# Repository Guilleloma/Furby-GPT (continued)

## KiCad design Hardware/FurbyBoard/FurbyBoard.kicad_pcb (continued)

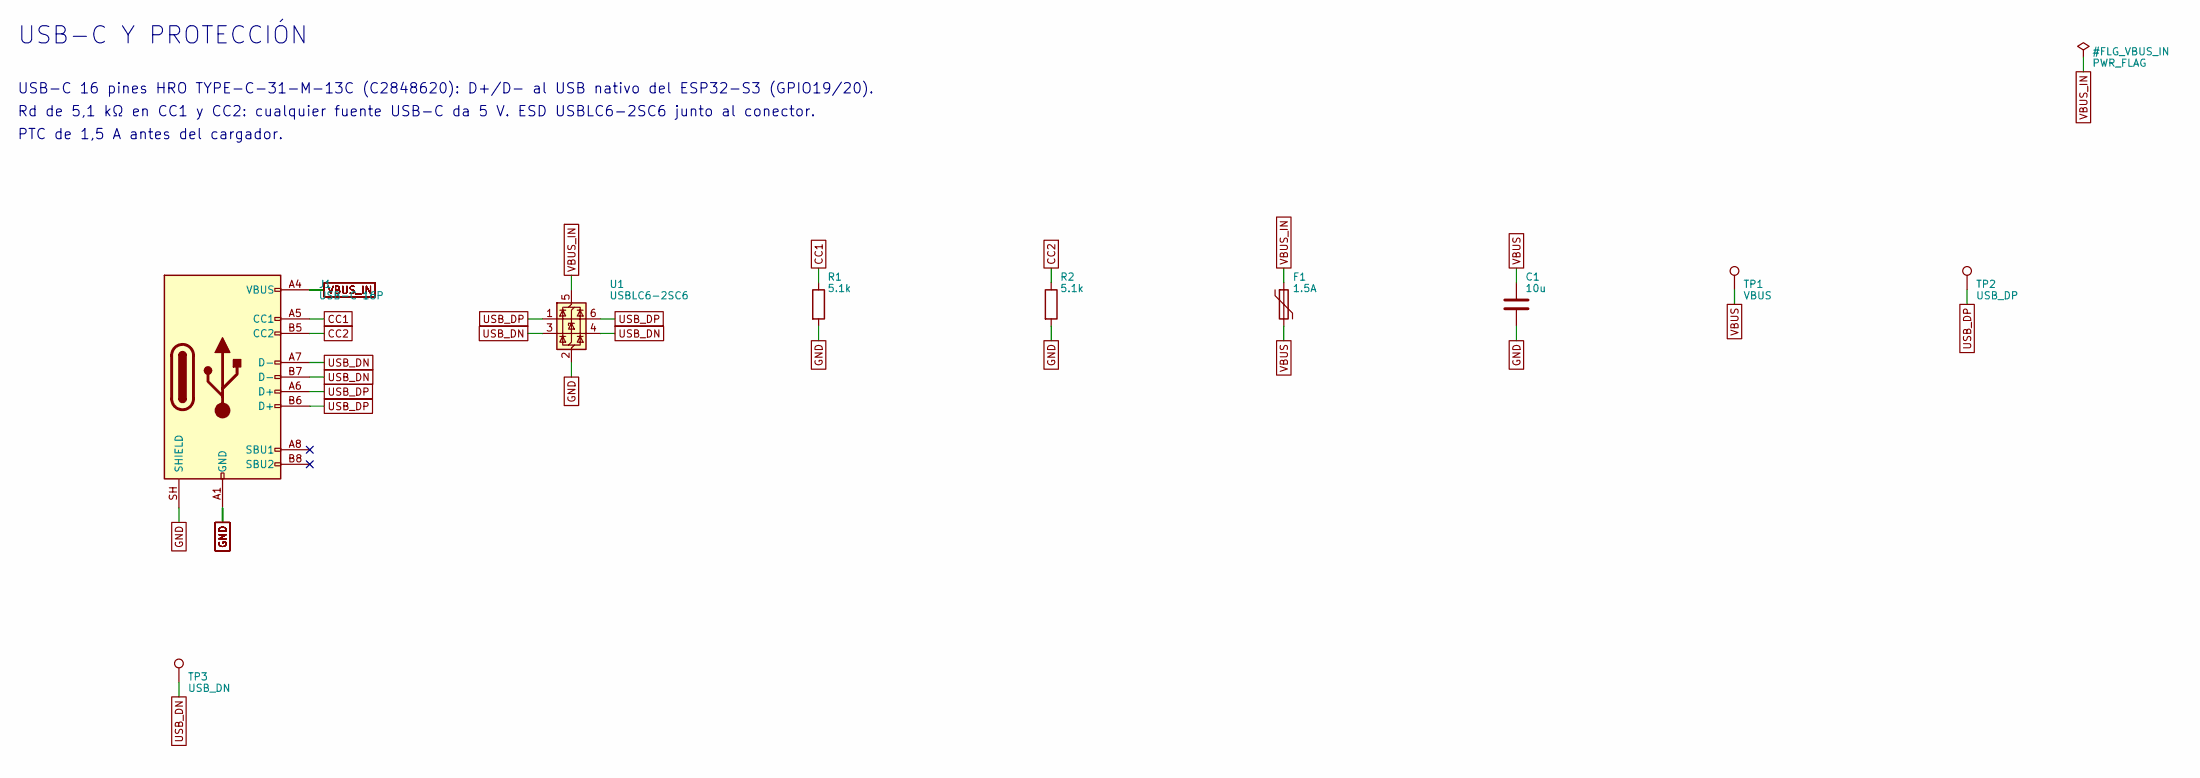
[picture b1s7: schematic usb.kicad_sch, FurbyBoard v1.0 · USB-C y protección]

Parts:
C1: 10u; C_0603_1608Metric; MPN 10 µF 10 V X5R; LCSC C19702
F1: 1.5A; Fuse_1206_3216Metric; MPN BSMD1206-150-16V; LCSC C883133
J1: USB-C 16P; USB_C_HRO_TYPE-C-31-M-13C; MPN HRO TYPE-C-31-M-13C; LCSC C2848620
R1, R2: 5.1k; R_0603_1608Metric; MPN UNI-ROYAL 0603 1%; LCSC C23186
TP1: VBUS; TestPoint_Pad_D1.5mm
TP2: USB_DP; TestPoint_Pad_D1.5mm
TP3: USB_DN; TestPoint_Pad_D1.5mm
U1: USBLC6-2SC6; SOT-23-6; MPN STMicro USBLC6-2SC6; LCSC C2687116

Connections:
CC1: J1.A5 (CC1), R1.1
CC2: J1.B5 (CC2), R2.1
GND: C1.2, J1.A1 (GND), J1.A12 (GND), J1.B1 (GND), J1.B12 (GND), J1.SH (SHIELD), R1.2, R2.2, U1.2 (GND); also elsewhere on the board
USB_DN: J1.A7 (D-), J1.B7 (D-), TP3.1, U1.3 (I/O2), U1.4 (I/O2); also elsewhere on the board
USB_DP: J1.A6 (D+), J1.B6 (D+), TP2.1, U1.1 (I/O1), U1.6 (I/O1); also elsewhere on the board
VBUS: C1.1, F1.2, TP1.1; also elsewhere on the board
VBUS_IN: F1.1, J1.A4 (VBUS), J1.A9 (VBUS), J1.B4 (VBUS), J1.B9 (VBUS), U1.5 (VBUS)

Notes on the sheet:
Rd de 5,1 kΩ en CC1 y CC2: cualquier fuente USB-C da 5 V. ESD USBLC6-2SC6 junto al conector.
PTC de 1,5 A antes del cargador.
USB-C 16 pines HRO TYPE-C-31-M-13C (C2848620): D+/D− al USB nativo del ESP32-S3 (GPIO19/20).
USB-C Y PROTECCIÓN

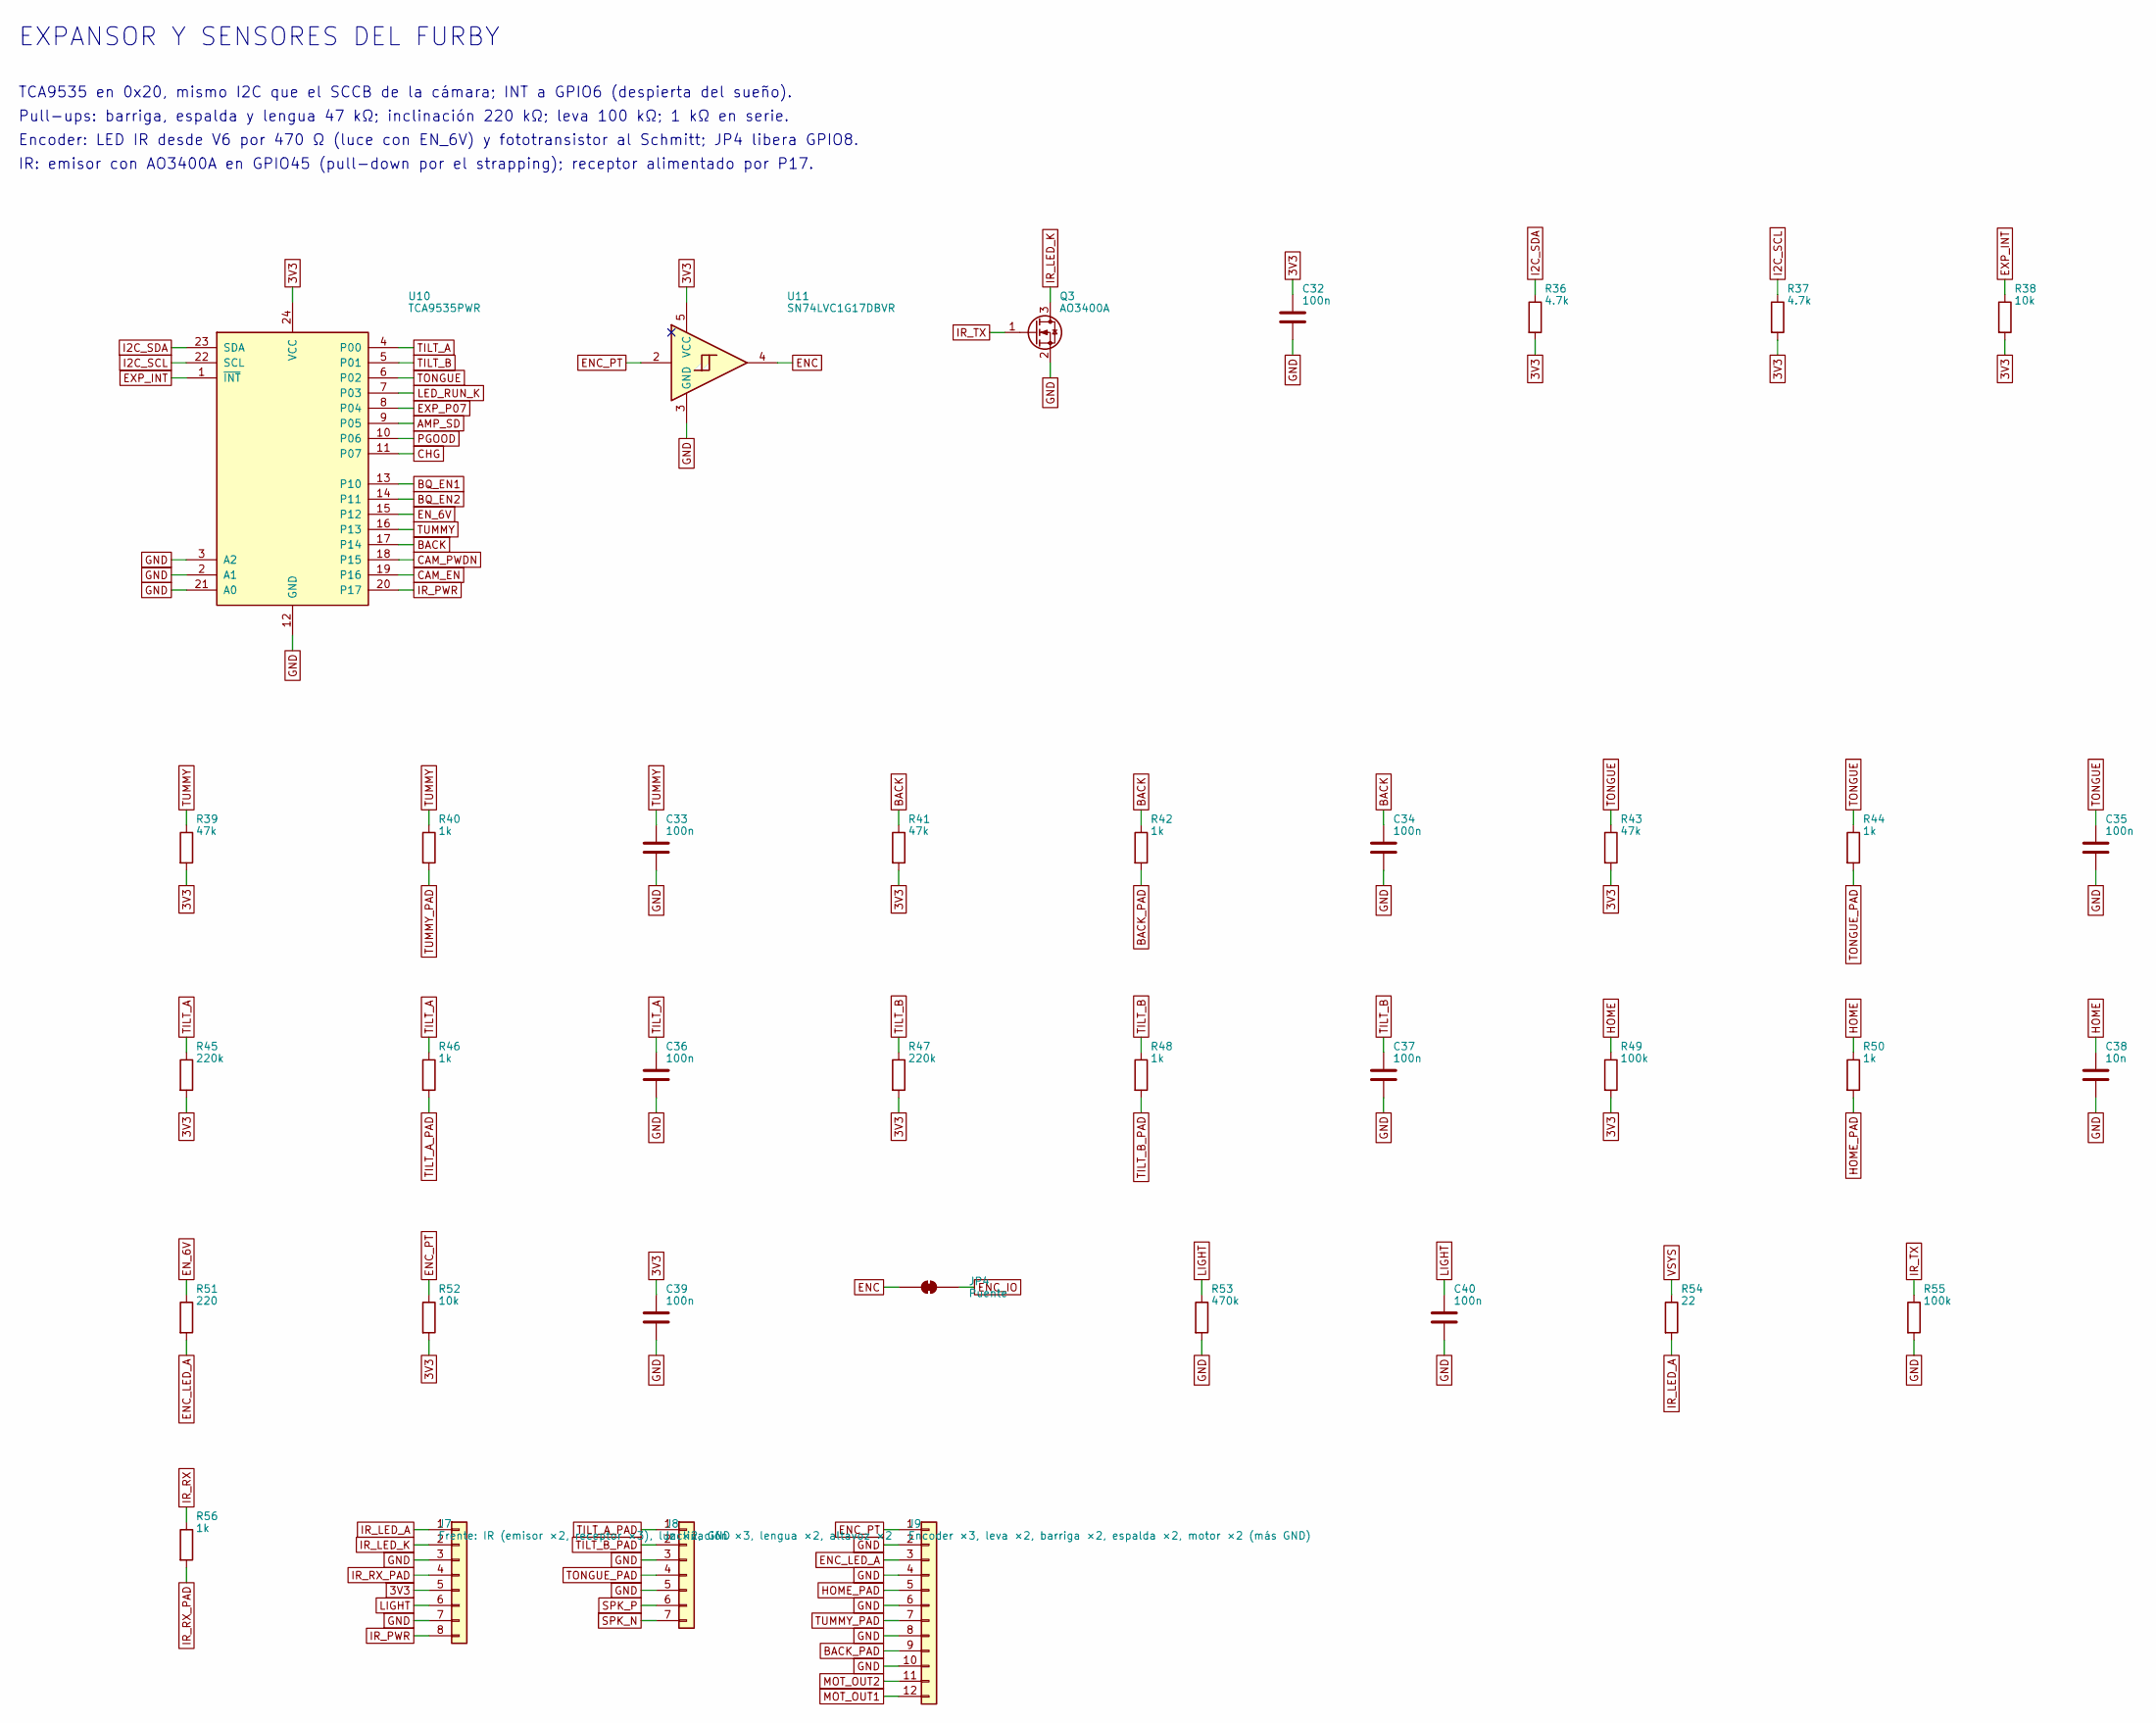
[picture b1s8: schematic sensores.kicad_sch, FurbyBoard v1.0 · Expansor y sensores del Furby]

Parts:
C32, C33, C34, C35, C36, C37, C39, C40: 100n; C_0603_1608Metric; MPN 100 nF 50 V X7R; LCSC C14663
C38: 10n; C_0603_1608Metric; MPN 10 nF 50 V X7R; LCSC C57112
J7: Frente: IR (emisor ×2, receptor ×3), luz ×2, GND; Pads_2x04_P2.54mm
J8: Inclinación ×3, lengua ×2, altavoz ×2; Pads_1x07_P2.54mm
J9: Encoder ×3, leva ×2, barriga ×2, espalda ×2, moto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; Pads_2x06_P2.54mm
JP4: Puente; SolderJumper-2_P1.3mm_Bridged_RoundedPad1.0x1.5mm
Q3: AO3400A; SOT-23; MPN AOS AO3400A; LCSC C20917
R36, R37: 4.7k; R_0603_1608Metric; MPN UNI-ROYAL 0603 1%; LCSC C23162
R38, R52: 10k; R_0603_1608Metric; MPN UNI-ROYAL 0603 1%; LCSC C25804
R39, R41, R43: 47k; R_0603_1608Metric; MPN UNI-ROYAL 0603 1%; LCSC C25819
R40, R42, R44, R46, R48, R50, R56: 1k; R_0603_1608Metric; MPN UNI-ROYAL 0603 1%; LCSC C21190
R45, R47: 220k; R_0603_1608Metric; MPN UNI-ROYAL 0603 1%; LCSC C22961
R49, R55: 100k; R_0603_1608Metric; MPN UNI-ROYAL 0603 1%; LCSC C25803
R51: 220; R_0603_1608Metric; MPN UNI-ROYAL 0603 1%; LCSC C22962
R53: 470k; R_0603_1608Metric; MPN UNI-ROYAL 0603 1%; LCSC C23178
R54: 22; R_0805_2012Metric; MPN UNI-ROYAL 0805W8F220JT5E; LCSC C17561
U10: TCA9535PWR; TSSOP-24_4.4x7.8mm_P0.65mm; MPN TI TCA9535PWR; LCSC C130204
U11: SN74LVC1G17DBVR; SOT-23-5; MPN TI SN74LVC1G17DBVR; LCSC C7836

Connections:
3V3: C32.1, C39.1, J7.5, R36.2, R37.2, R38.2, R39.2, R41.2, R43.2, R45.2, R47.2, R49.2, R52.2, U10.24 (VCC), U11.5 (VCC); also elsewhere on the board
AMP_SD: U10.9 (P05); also elsewhere on the board
BACK: C34.1, R41.1, R42.1, U10.17 (P14)
BACK_PAD: J9.9, R42.2
BQ_EN1: U10.13 (P10); also elsewhere on the board
BQ_EN2: U10.14 (P11); also elsewhere on the board
CAM_EN: U10.19 (P16); also elsewhere on the board
CAM_PWDN: U10.18 (P15); also elsewhere on the board
CHG: U10.11 (P07); also elsewhere on the board
ENC: JP4.1 (A), U11.4
ENC_IO: JP4.2 (B); also elsewhere on the board
ENC_LED_A: J9.3, R51.2
ENC_PT: J9.1, R52.1, U11.2
EN_6V: R51.1, U10.15 (P12); also elsewhere on the board
EXP_INT: R38.1, U10.1 (~INT); also elsewhere on the board
EXP_P07: U10.8 (P04); also elsewhere on the board
GND: C32.2, C33.2, C34.2, C35.2, C36.2, C37.2, C38.2, C39.2, C40.2, J7.3, J7.7, J8.3, J8.5, J9.2, J9.4, J9.6, J9.8, J9.10, Q3.2 (S), R53.2, R55.2, U10.2 (A1), U10.3 (A2), U10.12 (GND), U10.21 (A0), U11.3 (GND); also elsewhere on the board
HOME: C38.1, R49.1, R50.1; also elsewhere on the board
HOME_PAD: J9.5, R50.2
I2C_SCL: R37.1, U10.22 (SCL); also elsewhere on the board
I2C_SDA: R36.1, U10.23 (SDA); also elsewhere on the board
IR_LED_A: J7.1, R54.2
IR_LED_K: J7.2, Q3.3 (D)
IR_PWR: J7.8, U10.20 (P17)
IR_RX: R56.1; also elsewhere on the board
IR_RX_PAD: J7.4, R56.2
IR_TX: Q3.1 (G), R55.1; also elsewhere on the board
LED_RUN_K: U10.7 (P03); also elsewhere on the board
LIGHT: C40.1, J7.6, R53.1; also elsewhere on the board
MOT_OUT1: J9.12; also elsewhere on the board
MOT_OUT2: J9.11; also elsewhere on the board
PGOOD: U10.10 (P06); also elsewhere on the board
SPK_N: J8.7; also elsewhere on the board
SPK_P: J8.6; also elsewhere on the board
TILT_A: C36.1, R45.1, R46.1, U10.4 (P00)
TILT_A_PAD: J8.1, R46.2
TILT_B: C37.1, R47.1, R48.1, U10.5 (P01)
TILT_B_PAD: J8.2, R48.2
TONGUE: C35.1, R43.1, R44.1, U10.6 (P02)
TONGUE_PAD: J8.4, R44.2
TUMMY: C33.1, R39.1, R40.1, U10.16 (P13)
TUMMY_PAD: J9.7, R40.2
VSYS: R54.1; also elsewhere on the board

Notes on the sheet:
Pull-ups: barriga, espalda y lengua 47 kΩ; inclinación 220 kΩ; leva 100 kΩ; 1 kΩ en serie.
IR: emisor con AO3400A en GPIO45 (pull-down por el strapping); receptor alimentado por P17.
Encoder: LED IR desde V6 por 470 Ω (luce con EN_6V) y fototransistor al Schmitt; JP4 libera GPIO8.
TCA9535 en 0x20, mismo I2C que el SCCB de la cámara; INT a GPIO6 (despierta del sueño).
EXPANSOR Y SENSORES DEL FURBY

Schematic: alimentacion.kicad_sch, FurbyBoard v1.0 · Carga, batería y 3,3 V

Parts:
C2: 1u; C_0603_1608Metric; MPN 1 µF 50 V X5R; LCSC C15849
C3, C4, C6: 10u; C_0603_1608Metric; MPN 10 µF 10 V X5R; LCSC C19702
C5: 100n; C_0603_1608Metric; MPN 100 nF 50 V X7R; LCSC C14663
C7, C8: 22u; C_0805_2012Metric; MPN 22 µF 25 V X5R; LCSC C45783
D1: Rojo; LED_0603_1608Metric; MPN KT-0603R; LCSC C2286
D2: Verde; LED_0805_2012Metric; MPN KT-0805G; LCSC C2297
J2: BAT+; BAT_POS_Square3x3_Drill1.2
J3: BAT-; BAT_NEG_Round2.6_Drill1.0
L1: 0.47u; L_Changjiang_FHD4020S; MPN Changjiang FHD4020S-R47MT; LCSC C602026
Q1: SI7615ADN; Vishay_PowerPAK_1212-8_Single; MPN Vishay SI7615ADN-T1-GE3; LCSC C553966
R4: 1.8k; R_0603_1608Metric; MPN UNI-ROYAL 0603 1%; LCSC C4177
R5: 1.2k; R_0603_1608Metric; MPN UNI-ROYAL 0603 1%; LCSC C22765
R6, R7, R8, R9: 100k; R_0603_1608Metric; MPN UNI-ROYAL 0603 1%; LCSC C25803
R10, R11: 2.2k; R_0603_1608Metric; MPN UNI-ROYAL 0603 1%; LCSC C4190
R12: 10k; R_0603_1608Metric; MPN UNI-ROYAL 0603 1%; LCSC C25804
R13, R14: 470k; R_0603_1608Metric; MPN UNI-ROYAL 0603 1%; LCSC C23178
R15: 510k; R_0603_1608Metric; MPN UNI-ROYAL 0603 1%; LCSC C23192
R16: 91k; R_0603_1608Metric; MPN UNI-ROYAL 0603 1%; LCSC C23265
RT1: 10k NTC; R_0603_1608Metric; MPN Murata NCP18XH103F03RB; LCSC C13564
TP4: BAT; TestPoint_Pad_D1.5mm
TP5: VSYS; TestPoint_Pad_D1.5mm
TP6: 3V3; TestPoint_Pad_D1.5mm
U2: BQ24073RGTR; VQFN-16-1EP_3x3mm_P0.5mm_EP1.6x1.6mm; MPN TI BQ24073RGTR; LCSC C15220
U3: TPS63802DLAR; Texas_DLA_VSON-10_2x3mm_P0.5mm; MPN TI TPS63802DLAR; LCSC C2845237

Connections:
3V3: C7.1, C8.1, R8.2, R9.2, R15.1, TP6.1, U3.6 (VOUT); also elsewhere on the board
BAT: C4.1, Q1.1 (S), Q1.2 (S), Q1.3 (S), R13.1, TP4.1, U2.2 (BAT), U2.3 (BAT)
BAT_G: Q1.4 (G), R12.1
BAT_PAD: J2.1, Q1.5 (D)
BB_FB: R15.2, R16.1, U3.4 (FB)
BB_SW1: L1.1, U3.9 (L1)
BB_SW2: L1.2, U3.7 (L2)
BQ_EN1: R6.1, U2.6 (EN1); also elsewhere on the board
BQ_EN2: R7.1, U2.5 (EN2); also elsewhere on the board
BQ_ILIM: R5.1, U2.12 (ILIM)
BQ_ISET: R4.1, U2.16 (ISET)
BQ_TS: RT1.1, U2.1 (TS)
CHG: D1.1 (K), R9.1, U2.9 (~CHG); also elsewhere on the board
GND: C2.2, C3.2, C4.2, C5.2, C6.2, C7.2, C8.2, J3.1, R4.2, R5.2, R7.2, R12.2, R14.2, R16.2, RT1.2, U2.4 (~CE), U2.8 (VSS), U2.15 (TD), U2.17 (VSS), U3.2 (MODE), U3.3 (AGND), U3.8 (GND); also elsewhere on the board
LED_CHG_A: D1.2 (A), R10.2
LED_PG_A: D2.2 (A), R11.2
PGOOD: D2.1 (K), R8.1, U2.7 (~PGOOD); also elsewhere on the board
VBAT_SNS: C5.1, R13.2, R14.1; also elsewhere on the board
VBUS: C2.1, R10.1, R11.1, U2.13 (IN); also elsewhere on the board
VSYS: C3.1, C6.1, R6.2, TP5.1, U2.10 (OUT), U2.11 (OUT), U3.1 (EN), U3.10 (VIN); also elsewhere on the board

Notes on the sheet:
CARGA, BATERÍA Y 3,3 V
Al arrancar EN1=1, EN2=0: USB500 (475 mA). OUT = 4,4 V con USB y VBAT − 50 mV sin USB.
BQ24073: ICHG = 890/1,8k = 0,494 A; ILIM 1610/1,2k = 1,34 A con EN2=1 y EN1=0.
Q1 SI7615ADN: protección de polaridad con la puerta a GND. Con la batería al revés no llega
tensión negativa a nada; con USB, el BQ se queda en detección de cortocircuito (4–11 mA).
TPS63802: 3,3 V = 0,5 × (1 + 510k/91k). LED CHG y PG desde VBUS: no gastan batería.

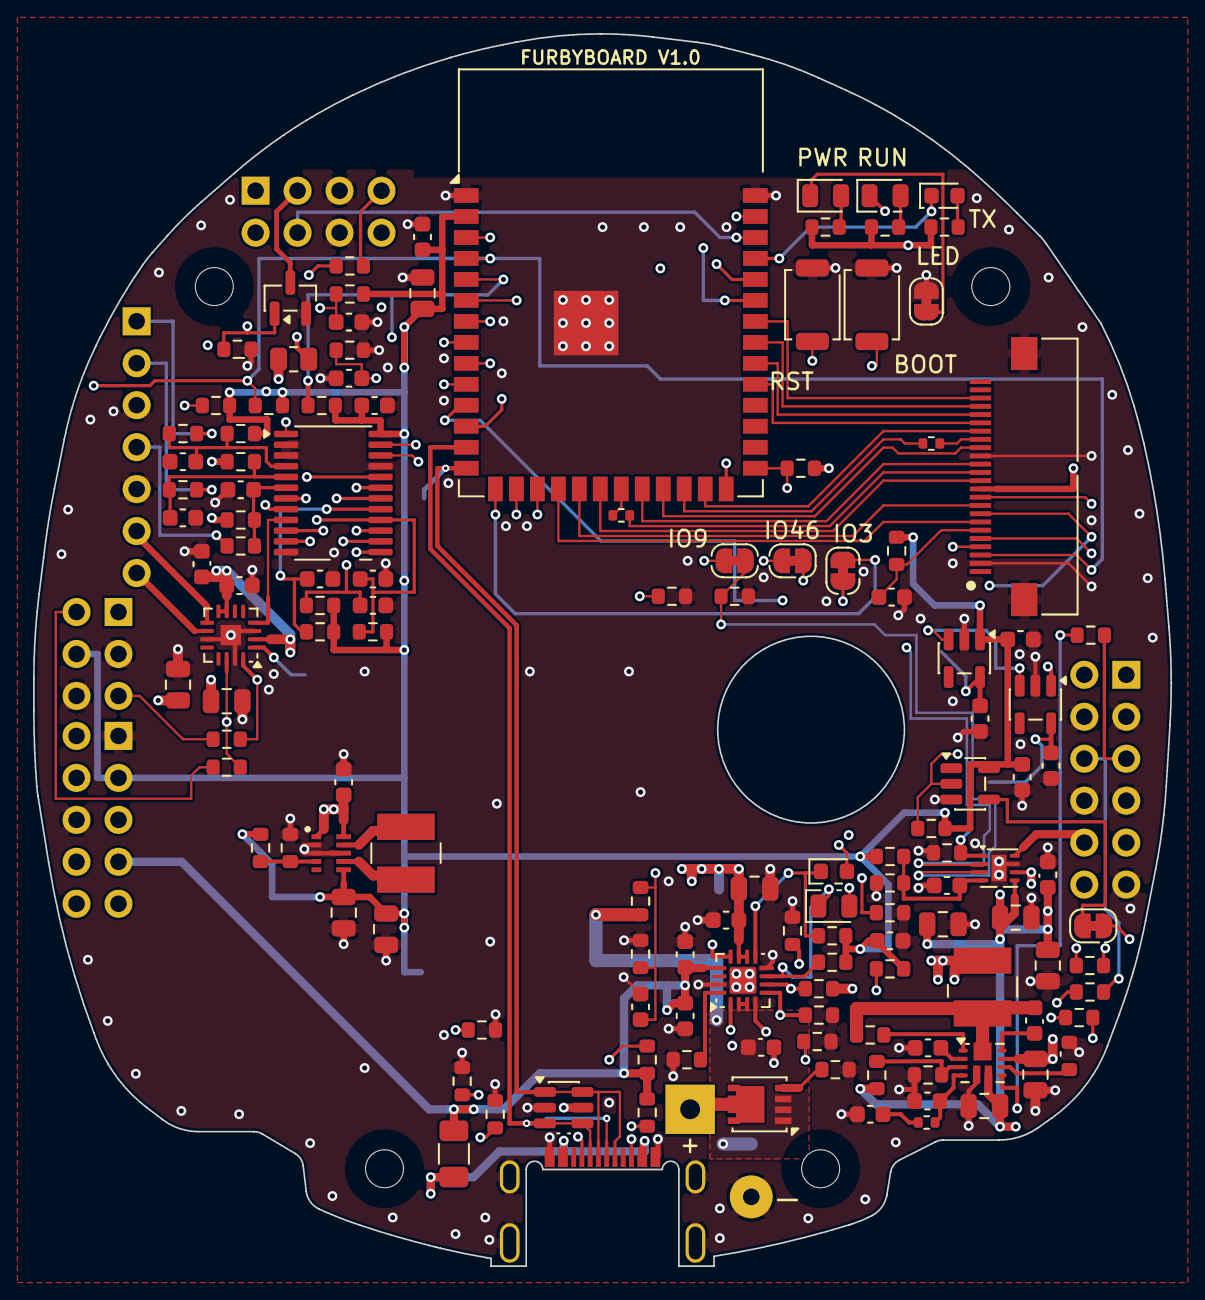
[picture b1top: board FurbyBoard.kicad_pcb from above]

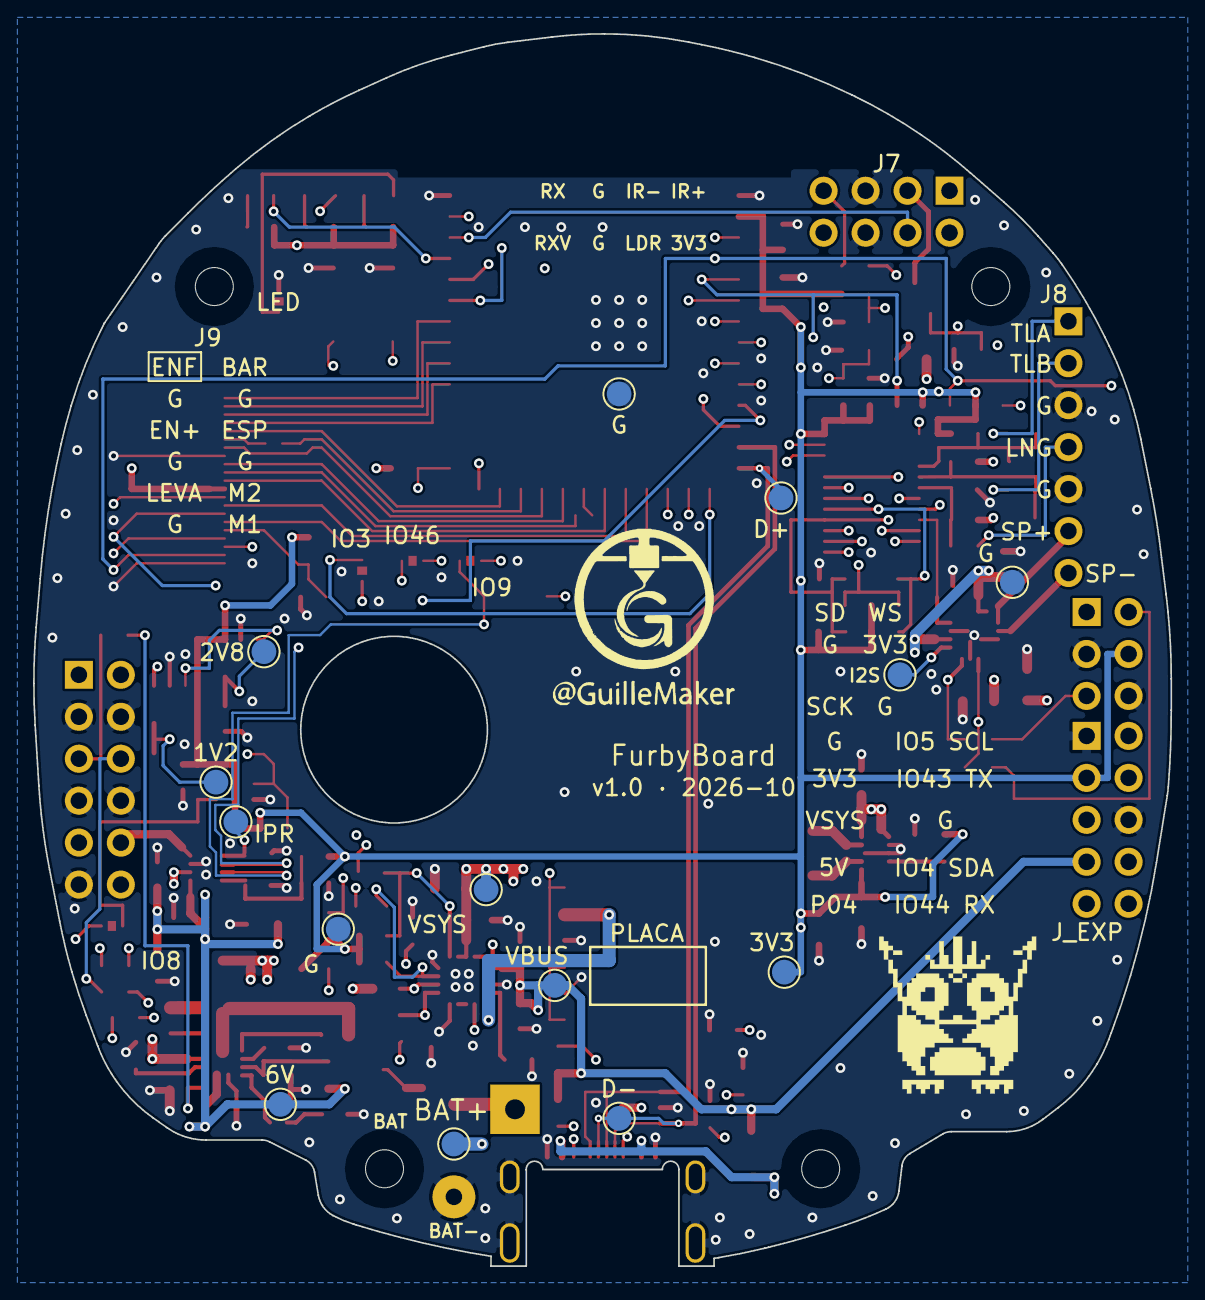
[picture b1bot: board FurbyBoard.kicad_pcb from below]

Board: 6 copper layers, 68.8 x 74.6 mm, 158 parts (16 on the bottom side), 108 nets.

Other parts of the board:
H1, H2, H3, H4: M2; MountingHole_2.3mm_M2
LOGO1: Logo_Furby_PixelArt
LOGO2: Logo_GuilleMaker

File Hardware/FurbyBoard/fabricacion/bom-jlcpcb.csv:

Comment,Designator,Footprint,LCSC Part #
10u,"C1,C3,C4,C6,C41",C_0603_1608Metric,C19702
1u,"C2,C11,C27,C28,C29",C_0603_1608Metric,C15849
100n,"C5,C10,C13,C22,C23,C26,C30,C31,C32,C33,C34,C35,C36,C37,C39,C40",C_0603_1608Metric,C14663
22u,"C7,C8,C9,C16,C17,C18,C19,C20,C21,C24,C25",C_0805_2012Metric,C45783
2.2u,C12,C_0603_1608Metric,C23630
4.7n,C14,C_0603_1608Metric,C53987
10p,C15,C_0603_1608Metric,C1634
10n,C38,C_0603_1608Metric,C57112
Rojo,"D1,D3",LED_0603_1608Metric,C2286
Verde,"D2,D4,D5",LED_0805_2012Metric,C2297
1.5A,F1,Fuse_1206_3216Metric,C883133
USB-C 16P,J1,USB_C_HRO_TYPE-C-31-M-13C,C2848620
FPC 24P 0.5,J6,FPC_AFC01-S24FCA-00,C262669
0.47u,L1,L_Changjiang_FHD4020S,C602026
1u,L2,L_Changjiang_FHD4020S,C602028
SI7615ADN,Q1,Vishay_PowerPAK_1212-8_Single,C553966
AO3400A,Q3,SOT-23,C20917
5.1k,"R1,R2",R_0603_1608Metric,C23186
1.8k,R4,R_0603_1608Metric,C4177
1.2k,R5,R_0603_1608Metric,C22765
100k,"R6,R7,R8,R9,R22,R25,R29,R30,R33,R49,R55",R_0603_1608Metric,C25803
2.2k,"R10,R11",R_0603_1608Metric,C4190
10k,"R12,R17,R18,R27,R34,R35,R38,R52",R_0603_1608Metric,C25804
470k,"R13,R14,R53",R_0603_1608Metric,C23178
510k,R15,R_0603_1608Metric,C23192
91k,R16,R_0603_1608Metric,C23265
1.5k,"R19,R28",R_0603_1608Metric,C22843
150k,R20,R_0603_1608Metric,C22807
390k,R21,R_0603_1608Metric,C23150
270k,R23,R_0603_1608Metric,C22965
30k,R24,R_0402_1005Metric,C25776
4.7k,"R26,R36,R37",R_0603_1608Metric,C23162
33,"R31,R32",R_0603_1608Metric,C23140
47k,"R39,R41,R43",R_0603_1608Metric,C25819
1k,"R40,R42,R44,R46,R48,R50,R56,R57,R58",R_0603_1608Metric,C21190
220k,"R45,R47",R_0603_1608Metric,C22961
220,R51,R_0603_1608Metric,C22962
22,R54,R_0805_2012Metric,C17561
33,"R59,R60",R_0402_1005Metric,C25105
10k NTC,RT1,R_0603_1608Metric,C13564
RESET / BOOT,"SW1,SW2",SW_SPST_TS-1088-xR020,C720477
USBLC6-2SC6,U1,SOT-23-6,C2687116
BQ24073RGTR,U2,VQFN-16-1EP_3x3mm_P0.5mm_EP1.6x1.6mm,C15220
TPS63802DLAR,U3,Texas_DLA_VSON-10_2x3mm_P0.5mm,C2845237
ESP32-S3-WROOM-1-N16R8,U4,ESP32-S3-WROOM-1,C2913202
TPS61089RNRR,U5,Texas_VQFN-RNR0011A-11,C165129
DRV8231ADSGR,U6,Texas_DSG0008A_WSON-8-1EP_2x2mm_P0.5mm_EP0.9x1.6mm,C5139865
MAX98357AETE+T,U7,TQFN-16-1EP_3x3mm_P0.5mm_EP1.23x1.23mm,C910544
ME6211C28M5G-N,U8,SOT-23-5,C53099
ME6211C12M5G-N,U9,SOT-23-5,C236672
TCA9535PWR,U10,TSSOP-24_4.4x7.8mm_P0.65mm,C130204
SN74LVC1G17DBVR,U11,SOT-23-5,C7836

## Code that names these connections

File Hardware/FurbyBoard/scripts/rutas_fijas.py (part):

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# ---------------------------------------------------------------- elevador de 6 V (TPS61089)
# Lazo de salida en F.Cu: pin 6 (VOUT) -> C18.1 y pin 5 (GND) -> C18.2 (C18 a 180°: V6 al este,
# GND al oeste; sin cruce ni vías dentro del lazo). SW: pad de L2, pad 11 y los stubs de C13 y RFSW.
# VSYS entra en C16.1 desde dos vías al este del pad (pin 9 con cuello de 0,25 de 1 mm). ILIM pasa
# entre los pads de C16 y EN_6V baja entre C18.1 y C16.2 hasta una vía (sigue por In2 a R25).
# Columna oeste (x -53,8): C12 (VCC), R22 (FB), C15 (COMP), R24 (COMP->RC) en filas de 1,6 mm con
# las pistas FSW (y -113,8), FB (y -115,4) y COMP (y -117,0) entre ellas; GND a vías en x -55,55.
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via("EN_6V", (-45.8, -89.6))
pista("EN_6V", "F.Cu", 0.2, (-45.8, -89.6), "R51.1")
# ---------------------------------------------------------------- buck-boost de 3,3 V (TPS63802)
# Cin (C6) sobre VIN (pines 1/10) con dos vías de VSYS; L1 al este con los nodos SW de 0,6; Cout
# (C7) bajo VOUT (pin 6) y C8 en paralelo; FB (R16/R15) al oeste. GND de los pines 2/3/8 unidos
# bajo el chip y a una vía; toma Kelvin de 3V3 para R15 desde el pad de C7 por B.Cu.
pista("BB_SW1", "F.Cu", 0.3, "U3.9", (-88.25, -102.3))
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pista("3V3", "F.Cu", 0.4, (-48.975, -97.42), "C27.1")
pista("3V3", "F.Cu", 0.4, "C27.1", "U8.1")
# ---------------------------------------------------------------- cargador (BQ24073)
# VSYS por los pines 10/11 a C3 y C17 y dos vías; VBUS por el pin 13 a C2.1/C1.1 (verticales) y una
# vía a B.Cu (TP1 sobre la fila; R10/R11 en F; F1.2 por B); BAT como polígono (2,9 A) de los pines
# 2/3 a C4 y Q1, con vías para TP4 y para la toma de R13 (B.Cu); ILIM por In2 a R5; ISET a R4; TS
# por In2 a RT1 con vías de retorno; EP con 4 vías térmicas (declaradas) y los pines 4/8/15 a vías.
pista("VSYS", "F.Cu", 0.25, "U2.10", "U2.11")
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stub("GND", "RT1.2", (0.0, 0.95), 0.3)
# ---------------------------------------------------------------- USB-C: VBUS_IN, CC1, CC2 y GND
# U1 (USBLC6) es de paso: los pines 6-1 (D+) y 4-3 (D-) se unen por debajo del cuerpo con 0,15,
# así que VBUS_IN no puede subir por el hueco entre columnas. Entra en el pin 5 y baja a In2 por
# una vía bajo el cuerpo (In2 hasta la vía de A4/B9). A4/B9 (0,3 centrada entre los dos pads) y
# A9/B4 bajan con sus propias vías a B.Cu (1 oz) y de ahí van a F1.1 por la fila y -120,9, sobre
# el borde de la ranura del conector y bajo el pad de escudo, con dos vías junto a F1.1. Antes iba
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pista("BOOT", "In2.Cu", 0.2, (-62.325, -80.7), (-62.325, -79.0), (-57.2, -73.875), (-57.2, -73.3))
via("BOOT", (-57.2, -73.3))
pista("BOOT", "F.Cu", 0.15, (-56.9, -73.3), "SW2.1")
# CAM_2V8 del pin 4: vía al oeste, In2 hasta U8.5 (TP10 en B.Cu) y C28.1; U9.1 con su propia vía a la
# misma columna de In2 (el tronco de 3V3 en F.Cu, x -48,975, cierra el paso entre U8 y U9)
pista("CAM_2V8", "F.Cu", 0.15, "J6.4", (-52.3, -84.25))
via("CAM_2V8", (-52.3, -84.25))
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via("CAM_2V8", (-46.55, -91.5))
pista("CAM_2V8", "In2.Cu", 0.25, (-46.55, -91.5), (-46.55, -90.4), (-47.25, -89.7), (-53.0, -89.7))
pista("CAM_2V8", "B.Cu", 0.2, (-51.512, -93.0), (-51.512, -92.088), "TP10.1")
# CAM_RST (pin 6) en F.Cu a R35.1 y, bajando a 45°, a C31.1
pista("CAM_RST", "F.Cu", 0.15, "J6.6", (-53.0, -83.25), (-55.075, -85.325), "R35.1", (-55.7, -86.225), "C31.1")
# CAM_EN: vía A junto a U8.3 y vía B sobre U9.3 (el resto de la red, por In2, en el bloque del expansor)
pista("CAM_EN", "F.Cu", 0.15, "U8.3", (-52.95, -89.862), (-53.5, -89.312), (-53.8, -89.312))
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via("GND", (-47.3, -90.9))
via("GND", (-48.25, -90.75))
# Puentes de soldadura (fila y -85,1 entre la banda DVP y el anillo del mecanismo; JP3 a 270° al
# este): IPROPI_IO / MOT_IN1_IO / MOT_IN2_IO desde los pines 15-17; JP1.2 -> R29.1 en F.Cu y
# JP2.2 -> R30.1 (bajo la batería) por In2 (los pull-down del puente H)
pista("IPROPI_IO", "F.Cu", 0.15, "U4.15", (-79.985, -82.3))
via("IPROPI_IO", (-79.985, -82.3))
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pista("GND", "F.Cu", 0.25, "U6.7", (-49.5, -103.45))
via("GND", (-49.5, -103.3))
via("GND", (-49.5, -104.1))
pista("IPROPI", "F.Cu", 0.25, "U6.1", ("R28.1", 0.0, -0.17))   # recto: R28 está 0,17 al norte del pin 1 (bloque M)
pista("IPROPI", "F.Cu", 0.25, "R28.1", (-51.825, -102.0))
via("IPROPI", (-51.825, -102.0))
pista("IPROPI", "B.Cu", 0.2, (-51.825, -102.0), (-51.3, -101.475), "TP8.1")
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via("GND", (-50.95, -102.2))
via("IPROPI", (-58.95, -87.55))
pista("IPROPI", "F.Cu", 0.2, (-58.95, -87.55), "JP3.2")
pista("MOT_VREF", "F.Cu", 0.25, "U6.4", ("C23.1", 0.0, 0.3))   # recto: C23 está 0,30 al sur del pin 4 (bloque M)
pista("MOT_VREF", "F.Cu", 0.25, "C23.1", (-51.875, -105.55), (-55.275, -105.55), "R27.1")
pista("MOT_VREF", "F.Cu", 0.2, "R27.1", "R26.2")
# Vías de GND de R28.2 y C23.2 en los extremos de la columna x -54,375 (paso 0,75); entre ellas, las de MOT_IN2 y
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stub("GND", "C20.2", (-1.05, 0.0), 0.3)
stub("GND", "C22.2", (0.0, 0.875), 0.3)
# ---------------------------------------------------------------- amplificador de clase D (MAX98357)
# VSYS por los pines 7/8 a C26.1 y a una vía; C25/C24 (bulk) con sus vías; GND de los pines 3/11/15
# al EP (1 vía). SPK_P/SPK_N (0,4) a J8.6/J8.7 en diagonales paralelas separadas.
pista("VSYS", "F.Cu", 0.25, "U7.7", "U7.8")
pista("VSYS", "F.Cu", 0.25, "U7.7", (-96.25, -87.2))
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pista("GND", "F.Cu", 0.25, "U7.15", (-95.75, -90.0))
via("GND", (-96.0, -89.6))
stub("GND", "C26.2", (0.0, 0.95), 0.3)
# C41 (10 µF, sim/RESULTADOS.md «Amplificador»): al oeste de C26, entre el tronco de VSYS de los pines 7/8 y SPK_P; su VSYS
# entra en el tronco por y -86,075 (≈ 2,5 mm de cobre hasta los pines) y su GND baja por una vía al oeste.
pista("VSYS", "F.Cu", 0.6, "C41.1", (-96.25, -86.075))
stub("GND", "C41.2", (-1.05, 0.0), 0.4)
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# con el lado del micro al oeste) y de ahí SCK_MIC/WS_MIC en F.Cu a J5.3/J5.4 (WS_MIC bordea J5 y
# J11 por el oeste). I2C: vías de los pines 4/5 → In2 (columnas x -84,3 / -83,9) a U10.23/22 y
# B.Cu (filas y -66,8 / -69,0) a R36.1/R37.1 (R36 y R37 intercambiados para que las filas aniden;
# J7.5 se alimenta por In2 por x -93,85 para dejar libre B.Cu). EXP_INT: vía del pin 6 → In2 por encima de todo
# (y -66,2) y columna x -84,8 a U10.1 y R38.1. EN: vía del pin 3 → In2 a R17/C11 (oeste) y a
# SW1 (este, fila y -63,6). AMP_SD en F.Cu por la columna x -93,75.
pista("I2S_BCLK", "F.Cu", 0.15, "U4.7", (-80.3, -70.61))
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pista("AMP_SD", "F.Cu", 0.25, "U7.4", (-93.75, -88.85), (-93.75, -87.3))
pista("AMP_SD", "F.Cu", 0.15, (-93.75, -87.3), (-93.75, -82.625), "U10.9")
# ---------------------------------------------------------------- sensado (clase D): VBAT_SNS, LIGHT, ENC_PT
# VBAT_SNS: pin 39 → vía bajo el módulo, In2 hacia el oeste (y -64,26), baja por x -78,0 y -80,6
# (único paso libre entre las filas del I2S y las vías de los pines 15-17) y diagonal hasta la
# vía junto a R13.2; el divisor R13/R14/C5 se encadena en F.Cu por x -70,3. LIGHT: pin 38 → vía,
# B.Cu por y -64,0 (entre J7 y la vía de EN) hasta J7.6 (THT) y de ahí por In2 a la vía junto a
# C40.1 (C40 a 180°, LIGHT al este, GND al oeste). ENC_PT: U11.2 ↔ R52.1 en F.Cu y vía a In2 por el hueco entre las
# filas de pads de J9 hasta J9.1 (THT).
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via("PGOOD", (-59.8, -104.98))
pista("PGOOD", "F.Cu", 0.2, (-59.8, -104.98), "D2.1")
# ---------------------------------------------------------------- barriga, espalda y cámara desde U10 (P13-P16)
# Vías bajo el cuerpo de U10 a la altura de su pin (stubs de F.Cu a 0,65 de las vías vecinas). TUMMY, BACK y
# CAM_PWDN suben por In3 al norte de U10 (x -90,8/-90,2/-89,6), van al este por y -75,95/-76,41/-76,87 entre
# las vías de 3V3 (-85,5) y GND (-83,1), bajan a 45° y cruzan bajo el módulo por y -77,45/-77,85/-78,25 (a más
# de 1 mm de la fila de VBAT_SNS en In2, cruces a 90° de las columnas del I2S); bajan por el canal x -48,95/
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via("3V3", (-85.5, -90.5))
# HOME: R49.1 y C38.1 se unen por el hueco entre las filas de C34/C33 y R49/C38 (y -87,0); del hueco entre columnas
# (x -89,0) sube a una vía bajo U10 y sigue por In2 (libre bajo U10: EXP_INT al norte, I2S al sur) hasta una vía junto
# al pin 11 del módulo (x -83,05, entre las columnas de I2C y la de I2S_DIN de In2).
pista("HOME", "F.Cu", 0.2, "R49.1", (-91.425, -87.0), (-88.175, -87.0), "C38.1")
pista("HOME", "F.Cu", 0.2, (-89.0, -87.0), (-89.0, -85.35))
via("HOME", (-89.0, -85.35))
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      (-83.05, -78.7), (-83.05, -76.6))
via("HOME", (-83.05, -76.6))
pista("HOME", "F.Cu", 0.2, "U4.11", (-83.05, -76.6))
# HOME hacia R50 (serie de J9.5): de la vía del pin 11 por B.Cu bajo el módulo (bolsa libre entre el tronco de 3V3 y
# IPROPI_IO) hasta una vía entre las filas MOT_IN de In2 y IPROPI_IO de B.Cu; por el interior de In3 (dentro del lazo de
# A1/A2) rodea el agujero del mecanismo por el oeste y el sur (a >= 0,6 mm del borde, entre el agujero y EN_6V) hasta una
# vía al SE; de ahí por In2 al sur y al este por y -106,2 hasta una vía al oeste de R50.1.
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# J9.11 al canal de J9 (x -43,07) y por la franja entre J9 y JP4 (y -105,95) a JP4.1.
pista("ENC", "F.Cu", 0.2, "U11.4", (-49.0, -99.55), (-49.0, -100.9), (-43.07, -100.9), (-43.07, -105.95),
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
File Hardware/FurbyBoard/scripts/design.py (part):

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    # GPIO por geometría (replanteo del 2026-10-24): la cámara en los pines del lado del FPC
    # (fila inferior derecha y columna derecha, en el orden de los pads de J6), y en la columna
    # izquierda, de arriba abajo, lo que va al expansor (I2C, INT), al amplificador y al micro
    # (I2S) y a J9 por el pasillo sur (HOME, ENC). Los pines 35-39 (IR_RX, UART0, LIGHT,
    # VBAT_SNS) salen por debajo del módulo en capas internas: no cruzan el bus de la cámara.
    # Sin tocar strapping (IO0, IO3, IO45, IO46) ni el USB (IO19/IO20).
    # Pin 21: CAM_XCLK_IO es el tramo corto hasta la serie R59 (33 Ω, junto al pin); del otro lado
    # de R59 sigue CAM_XCLK hasta J6 (M7, 2026-10-27).
    io = {
        "1": "GND", "2": "3V3", "3": "EN", "4": "I2C_SDA", "5": "I2C_SCL", "6": "EXP_INT",
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    R("R28", s, "1.5k", "IPROPI", "GND", "RIPROPI: 2,25 V por amperio")
    R("R29", s, "100k", "MOT_IN1", "GND", "Motor parado al arrancar")
    R("R30", s, "100k", "MOT_IN2", "GND", "Motor parado al arrancar")
    JP("JP1", s, "MOT_IN1_IO", "MOT_IN1", "Cortar para liberar GPIO9")
    JP("JP2", s, "MOT_IN2_IO", "MOT_IN2", "Cortar para liberar GPIO46")
    JP("JP3", s, "IPROPI_IO", "IPROPI", "Cortar para liberar GPIO3 (ADC)")
    TP("TP7", s, "V6", "5,94 V con EN_6V")
    TP("TP8", s, "IPROPI", "2,25 V/A")

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    C("C24", s, "22u", "VSYS", "GND", "VDD del amplificador")
    C("C25", s, "22u", "VSYS", "GND", "VDD del amplificador")
    C("C26", s, "100n", "VSYS", "GND", "VDD del amplificador")
    # 10 µF junto a los pines 7/8 (sim/RESULTADOS.md, «Amplificador»): C24/C25 quedan al otro lado del puente de VSYS
    # de B.Cu y con solo C26 el rizado en VDD era de 257 mV pp; la hoja pide 0,1 µF + 10 µF en VDD
    C("C41", s, "10u", "VSYS", "GND", "VDD del amplificador, junto a los pines 7/8")
    R("R31", s, "33", "I2S_BCLK", "I2S_SCK_MIC", "Serie hacia el micro (cable)")
    R("R32", s, "33", "I2S_WS", "I2S_WS_MIC", "Serie hacia el micro (cable)")
    pads("J5", s, ["I2S_DIN", "GND", "I2S_SCK_MIC", "I2S_WS_MIC", "3V3", "GND"], "FurbyBoard:Pads_2x03_P2.54mm",
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    # 33 Ω amortigua sin pasarse; con ≈ 10 pF de carga, τ = 0,33 ns frente a 50 ns de periodo a
    # 20 MHz. HREF y VSYNC (frecuencia de línea y de cuadro) y los datos (se muestrean a mitad de
    # periodo de PCLK, con tiempo de sobra para que se asiente el flanco) no la llevan (NOTAS.md).
    R0402("R59", s, "33", "CAM_XCLK_IO", "CAM_XCLK", "Serie del reloj XCLK, junto al pin 21 del módulo")
    R0402("R60", s, "33", "CAM_PCLK", "CAM_PCLK_CAM", "Serie del reloj PCLK, junto al pad 17 de J6 (pad 2 al este, hacia J6)")
    part("U8", s, "Regulator_Linear:ME6211C28M5", "ME6211C28M5G-N", "Package_TO_SOT_SMD:SOT-23-5",
         {"1": "3V3", "2": "GND", "3": "CAM_EN", "4": "", "5": "CAM_2V8"},
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    part("U10", s, "Interface_Expansion:TCA9535PWR", "TCA9535PWR", "Package_SO:TSSOP-24_4.4x7.8mm_P0.65mm",
         # Puertos por geometría (2026-10-24): P0x (cara oeste) hacia J8, J11, J7 y el
         # amplificador; P1x (cara este) hacia el cargador, el elevador, J9, la cámara y el LED.
         # Bloque U2 (2026-10-25): P03 LED_RUN_K, P04 EXP_P07 y P17 IR_PWR (ver NOTAS «Pines»).
         {"1": "EXP_INT", "2": "GND", "3": "GND", "4": "TILT_A", "5": "TILT_B", "6": "TONGUE",
          "7": "LED_RUN_K", "8": "EXP_P07", "9": "AMP_SD", "10": "PGOOD", "11": "CHG", "12": "GND",
          "13": "BQ_EN1", "14": "BQ_EN2", "15": "EN_6V", "16": "TUMMY", "17": "BACK",
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         {"1": "", "2": "ENC_PT", "3": "GND", "4": "ENC", "5": "3V3"}, "C7836", "ext",
         "TI SN74LVC1G17DBVR", "Schmitt del encoder")
    C("C39", s, "100n", "3V3", "GND", "Desacoplo del Schmitt")
    JP("JP4", s, "ENC", "ENC_IO", "Cortar para liberar GPIO8")
    # Luz: LDR entre 3V3 y LIGHT, 470k a GND
    R("R53", s, "470k", "LIGHT", "GND", "LDR con luz ≈ 7 µA")
    C("C40", s, "100n", "LIGHT", "GND", "Filtro del ADC")
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         "UNI-ROYAL 0805W8F220JT5E", "LED IR ≈ 100 mA en pulsos (0805 por la potencia de pico)")
    part("Q3", s, "Transistor_FET:Q_NMOS_GSD", "AO3400A", "Package_TO_SOT_SMD:SOT-23",
         {"1": "IR_TX", "2": "GND", "3": "IR_LED_K"}, "C20917", "base", "AOS AO3400A", "Emisor IR")
    R("R55", s, "100k", "IR_TX", "GND", "GPIO45 a 0 al arrancar (strapping VDD_SPI)")
    R("R56", s, "1k", "IR_RX", "IR_RX_PAD", "Serie del receptor IR")
    # Pads de cables (agrupados como en la planta)
    # J7.3 y J7.8 permutados (bloque U2, 2026-10-25): IR_PWR sale por el sur de J7 hacia In2.
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
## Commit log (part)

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2023-11-14 Files version 0.1
    All the files for the first Beta Version
2023-11-14 text to see how the commits works
2023-11-24 Aniado version 1.0
2023-11-24 Limpio readme
2023-11-29 actualizo a la version 1.1
2023-12-02 control de motor segun estado Dormido y Despierto, el control se realiza por tiempo de giro de motor
2023-12-02 Update README.md
    Updated the default description
2023-12-20 Cambios en los tiempos de respuesta, use de Wav en lugar de MP3 y secuencias de moviemientos, optimizacion de codigo
2023-12-21 Resultos conflictos de stream closed
2024-02-16 Update README.md
    Add Hardware required in requirements
2024-02-16 Update elabapikey.txt
    Removed private key
2024-02-16 Removed private key
2024-03-15 Added example to test Motors
2024-03-21 Create Document Folder
2024-03-22 Rename WhatsApp Image 2024-03-22 at 01.04.49.jpeg to Furby GPT Base.jpeg
2024-03-22 Update text_to_speech.py
    Removed personal json path
